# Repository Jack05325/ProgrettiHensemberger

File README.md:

# Progetti ITI P. Hensemberger

Benvenuto in questa repository! Qui troverai una raccolta di progetti che ho realizzato per l'**ITI P. Hensemberger**.

## Contenuti
La repository include:

- **PCB**: Circuiti stampati progettati per diversi scopi.
- **Schemi elettronici**: Diagrammi dettagliati di circuiti per vari progetti.
- **Librerie per Arduino**: Software scritto per estendere le funzionalità di Arduino.
- **Altro**: Risorse utili e sperimentazioni varie legate al mondo dell'elettronica e della programmazione.

## Come usare questa repository

1. Esplora le cartelle per trovare ciò che ti interessa.
2. Ogni progetto include file e documentazione per aiutarti a capirne il funzionamento e ad utilizzarlo.

## Nota sulla documentazione

La documentazione per alcuni progetti non è ancora completa, ma verrà presto aggiornata e completata.

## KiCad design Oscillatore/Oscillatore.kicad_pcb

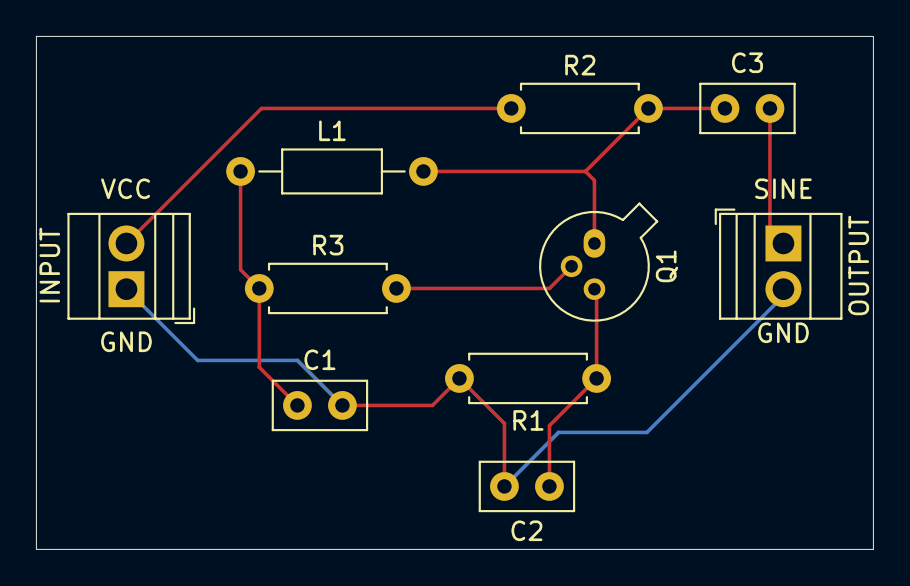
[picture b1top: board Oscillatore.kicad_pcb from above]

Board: 2 copper layers, 46.5 x 28.5 mm, 10 parts (0 on the bottom side), 7 nets.

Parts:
C1, C3: 33uF; C_Disc_D5.0mm_W2.5mm_P2.50mm
C2: 1uF; C_Disc_D5.0mm_W2.5mm_P2.50mm
INPUT: Screw_Terminal_01x02; TerminalBlock_Xinya_XY308-2.54-2P_1x02_P2.54mm_Horizontal
L1: 4uH; L_Axial_L5.3mm_D2.2mm_P10.16mm_Horizontal_Vishay_IM-1
OUTPUT: Screw_Terminal_01x02; TerminalBlock_Xinya_XY308-2.54-2P_1x02_P2.54mm_Horizontal
Q1: NPN; TO-18-3
R1: 470; R_Axial_DIN0207_L6.3mm_D2.5mm_P7.62mm_Horizontal
R2: 10K; R_Axial_DIN0207_L6.3mm_D2.5mm_P7.62mm_Horizontal
R3: 2.2K; R_Axial_DIN0207_L6.3mm_D2.5mm_P7.62mm_Horizontal

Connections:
GND: C1.2, C2.2, INPUT.1, OUTPUT.2, R1.2
unnamed: C1.1, L1.1, R3.1
unnamed: C3.2, OUTPUT.1
unnamed: Q1.2 (B), R3.2
unnamed: C3.1, L1.2, Q1.1 (C), R2.2
unnamed: C2.1, Q1.3 (E), R1.1
VCC: INPUT.2, R2.1

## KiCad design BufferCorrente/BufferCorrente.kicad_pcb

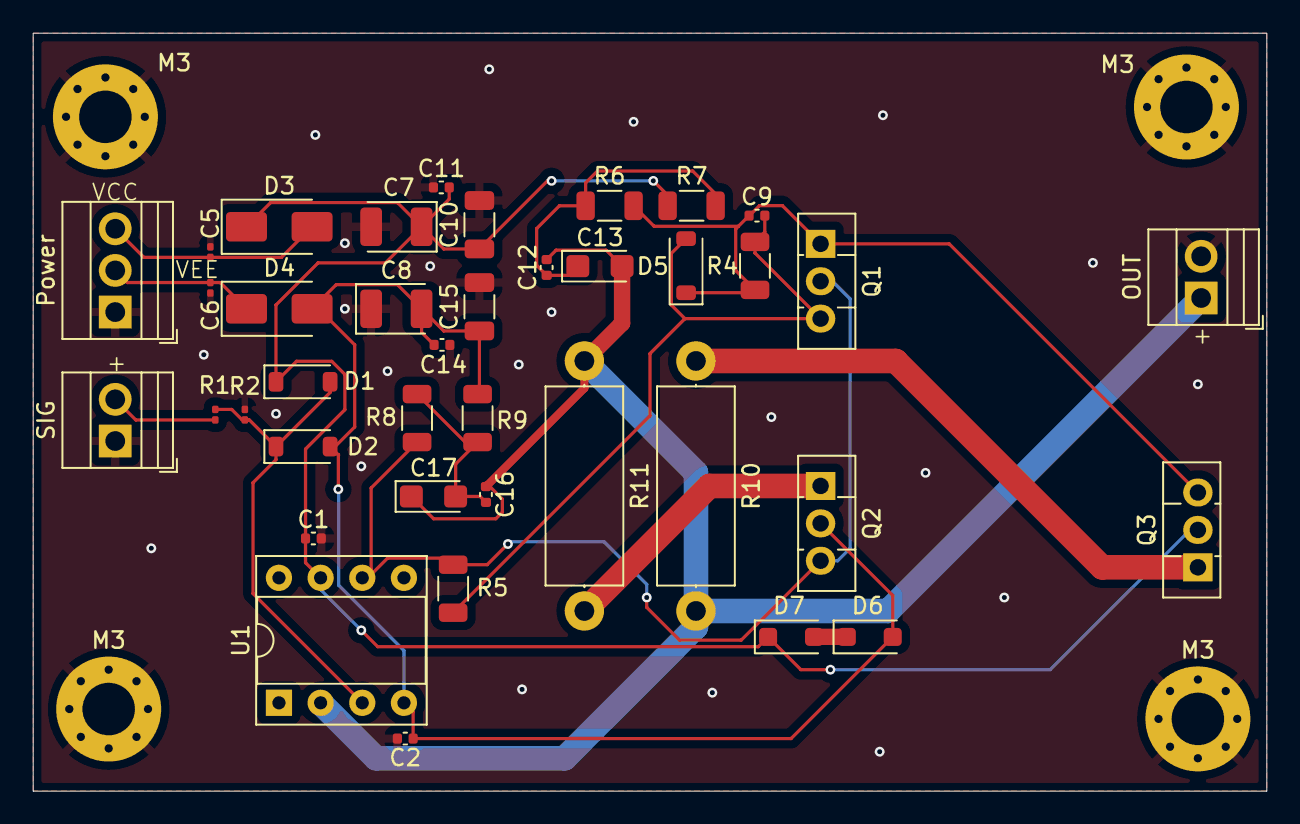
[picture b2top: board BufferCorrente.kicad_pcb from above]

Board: 2 copper layers, 75.2 x 46.2 mm, 43 parts (0 on the bottom side), 16 nets.

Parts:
C1, C2: 10nF; C_0402_1005Metric
C5, C6: 220nF; C_0201_0603Metric
C7, C8: 10uF; CP_EIA-3528-21_Kemet-B
C9, C11, C12, C14, C16: 100nF; C_0402_1005Metric
C10, C15: 10uF; C_1206_3216Metric
C13, C17: 22uF; CP_EIA-3216-18_Kemet-A
D1, D2, D5: 1N4148; D_SOD-123
D3, D4: 1N4007; D_SMA
D6, D7: D; D_SOD-123F
M3, M3#2, M3#3, M3#4: MountingHole_Pad; MountingHole_3.2mm_M3_Pad_Via
OUT: OUTPUT; TerminalBlock_Xinya_XY308-2.54-2P_1x02_P2.54mm_Horizontal
Power: Differenzial; TerminalBlock_Xinya_XY308-2.54-3P_1x03_P2.54mm_Horizontal
Q1, Q2, Q3: BD138; TO-126-3_Vertical
R1: 220; R_0201_0603Metric
R2: 22K; R_0201_0603Metric
R4: 1K; R_1206_3216Metric
R5: 560; R_1206_3216Metric
R6, R7, R8, R9: 2.2K; R_1206_3216Metric
R10, R11: 1; R_Axial_DIN0414_L11.9mm_D4.5mm_P15.24mm_Horizontal
SIG: INPUT; TerminalBlock_Xinya_XY308-2.54-2P_1x02_P2.54mm_Horizontal
U1: OPA134; DIP-8_W7.62mm_Socket

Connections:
+16V: C1.1, C7.1, C10.1, C11.2, D1.1 (K), D3.1 (K), D7.1 (K), Q3.2 (C), R7.1, U1.7 (V+)
-16V: C2.1, C8.2, C14.1, C15.1, D2.2 (A), D4.2 (A), D6.2 (A), Q2.2 (C), R9.2, U1.4 (V-)
GND: C1.2, C2.2, C5.2, C6.1, C7.2, C8.1, C10.2, C11.1, C14.2, C15.2, M3.1, M3#2.1, M3#3.1, M3#4.1, OUT.2, Power.1, R2.2, SIG.1
unnamed: C12.1, C13.1, R6.1, R7.2
unnamed: C16.2, C17.2, R8.2, R9.1
unnamed: D1.2 (A), D2.1 (K), R1.2, R2.1, U1.3 (+)
unnamed: C9.2, D5.2 (A), Q1.3 (B), R4.2, R5.1
unnamed: C9.1, D5.1 (K), Q1.1 (E), Q3.3 (B), R4.1, R6.2
unnamed: D6.1 (K), D7.2 (A)
unnamed: R1.1, SIG.2
unnamed: C12.2, C13.2, C16.1, C17.1, OUT.1, R10.2, R11.1, U1.2 (-)
unnamed: Q1.2 (C), Q2.3 (B), R5.2, R8.1, U1.6
unnamed: Q2.1 (E), R11.2
unnamed: Q3.1 (E), R10.1
VCC: C5.1, D3.2 (A), Power.3
VEE: C6.2, D4.1 (K), Power.2

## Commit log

2025-01-08 Iniziallizazione dei progetti: Oscillatore, libreria Hamming.h, Ricevitore RF AM, Buffer corrente
2025-01-08 Inserimento sorgente libreria Hamming.h
2025-01-15 Implementato brute forcing del cifrario di cesare
2025-02-02 Aggiornata la PCB del buffer in corrente con coponenti SMD e groud plane
